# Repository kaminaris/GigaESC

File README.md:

# GigaESC - 40s 400A

GigaESC - Based upon the VESC®*-Project VESC is a registered TM, owned by Benjamin Vedder

* Modular design
* Logic board
* Separate Power Stage (Mosfet) board
* 40s capable
* Up to 188V (Mosfets and caps up to 200V)
* Up to 300A (depending on choice of mosfets)
* Hall sensor current measurement or low side shunts
* Built in IMU - LSM6DS3TR-C
* Optional Hardware current protection
* Designed for easy manufacturing at JLCPcb (KiCad Fabrication Toolkit)

Licensed under [Creative Commons Attribution-NonCommercial-ShareAlike 4.0 International License](https://creativecommons.org/licenses/by-nc-sa/4.0/legalcode.en)

# ⚠️Please do not order before contacting me on discord️⚠️

https://discord.gg/embedded

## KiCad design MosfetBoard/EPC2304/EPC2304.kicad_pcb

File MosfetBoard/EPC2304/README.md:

# GigaESC - EPC2304

---

# ⚠️Please do not order before contacting me on discord️⚠️

this is a very hard board to solder requires:

- Good knowledge of microsoldering
- **A microscope**
- Hot air capable of reaching 450°C
- A very thin soldering iron tip
- An oscilloscope

## GaN Soldering procedure

Use 60/40 solder from a reputable source. Trying to use lead-free solder by hand will be extremely difficult. Using poor-quality products will also result in failure, and this applies to flux as well.

This board has 4 layers, so it can absorb a lot of heat. Using high-quality solder is essential because the board is very sensitive to cold joints.

Having a good soldering iron is crucial and can make the difference between success and failure.

To solder GaN mosfets i strongly recommend using soldering paste instead, everything else can be done with wire tin.

1. Apply solder paste with flux on the footprint.
2. Position the GaN mosfet in place.
3. Use hot air until the solder melts and the GaN device is securely in place, applying gentle pressure to ensure proper contact.
4. Remove any excess solder with a soldering iron.
5. Allow the solder to cool down.

**[Repeat]**

1. Heat the solder joint again with hot air.
2. Apply flux.
3. Use tweezers to gently swirl the MOSFET, ensuring each pad has an equal amount of solder.
4. Reposition the MOSFET properly.
5. Allow the solder to cool down.

**[Repeat until the GaN mosfet self-aligns perfectly.]**

**⚠️While doing soldering procedure, make sure there are no microblobs of solder underneath mosfets.**
This may take a couple of tries to get it right.

## Testing procedure

1. Check with a multimeter the following parameters:
    - Resistance between + and - terminals: Should be very high, nearly open loop.
    - Resistance between each phase to ground: Should be greater than 40 kOhms.
    - Resistance between each phase to VBat+: Should be in the megaohms range.
    - Phase comparison: Each phase should have similar resistance readings to the others.
    - Gate connection check: Ensure each gate connects to the main PL and PH lines (this can be verified from the top of the PCB).
2. If electrically everything seems fine, connect to the main board and turn on the VESC:
    - Error code check: If any error code appears, there may be an issue, most commonly cold joints.
    - Current offset measurement:
        - Measure current offsets before doing anything with the VESC. 
        - They should all be within +/-10 LSB and around 2070
         
3. Connect the motor and measure its RL properties:
    - If you observe any abnormal values, such as very high inductance:
       - Check and fix any cold joints.
       - Use a multimeter to ensure each current sensor at idle is outputting about 1.65V.
       - Ensure each current sensor is receiving 5V.
4. Once any initial problems are resolved:
    - Set the current to the lowest possible value in FOC -> General and perform a full detection until all parameters are green and appear reasonable:
    
    - If you have another VESC, compare results with it. It will depend on motor itself so do not compare them to mine.
    - Perform a short double pulse test, for example: double_pulse 100 10 5 10. Confirm both edges look okay and are not overshooting.
    - Perform the motor detection.

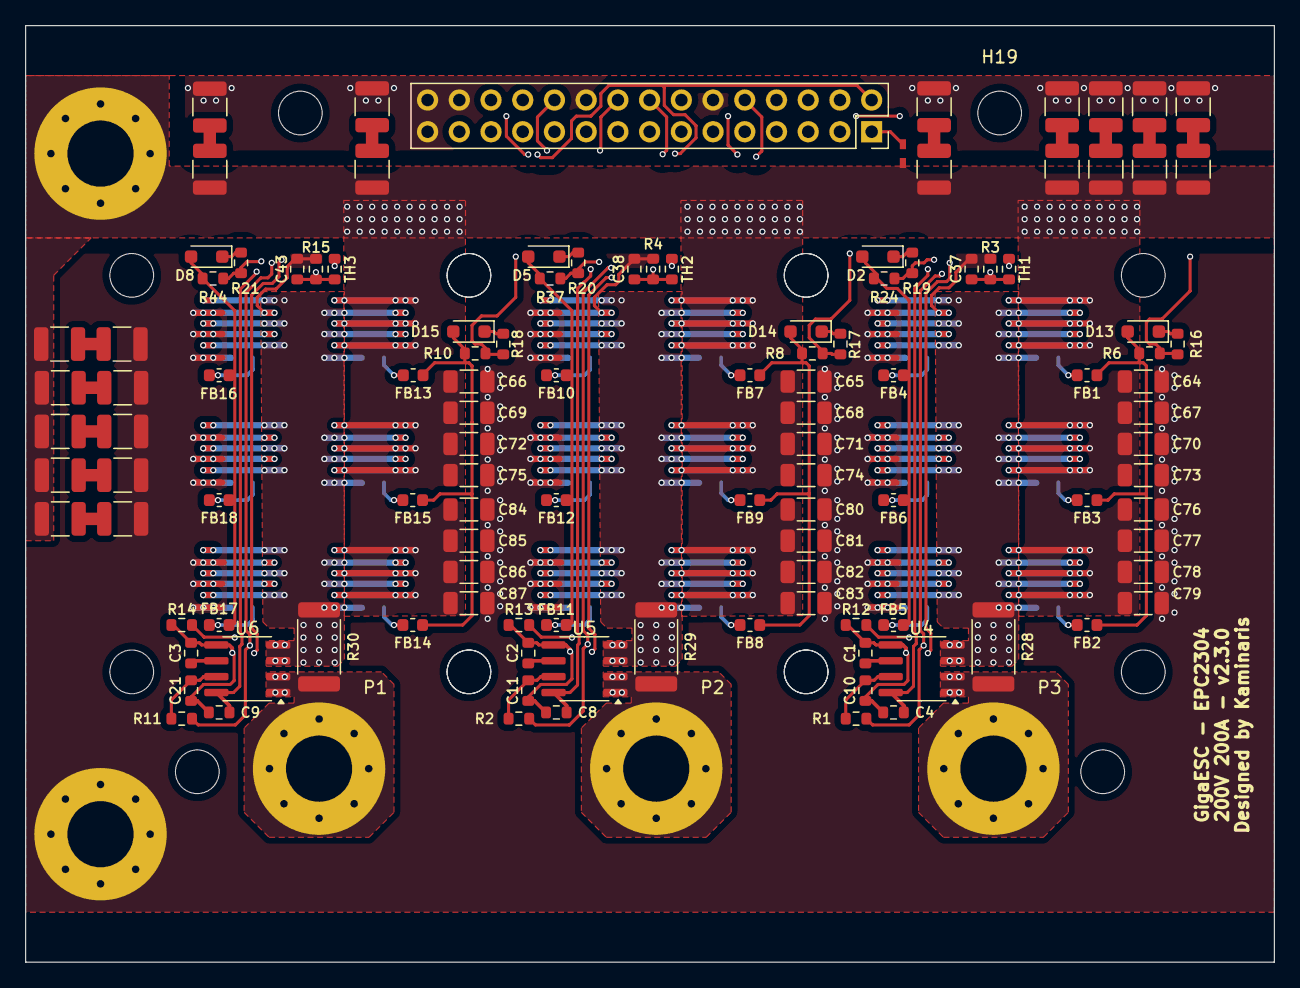
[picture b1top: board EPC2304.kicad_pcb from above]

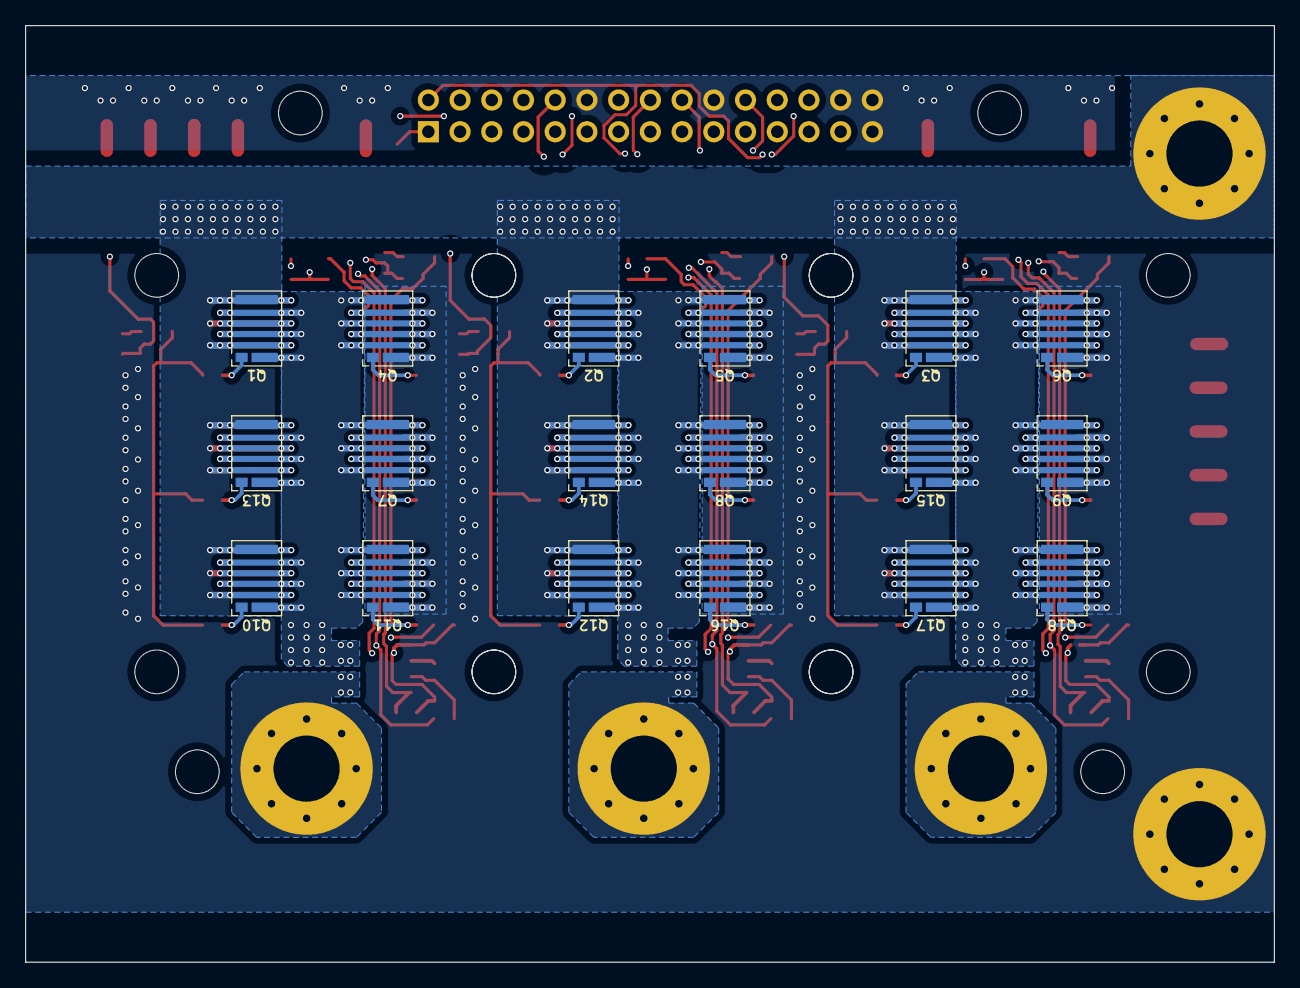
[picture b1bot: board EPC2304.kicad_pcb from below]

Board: 4 copper layers, 100.0 x 75.0 mm, 155 parts (18 on the bottom side), 74 nets.

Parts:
C1, C2, C3: 10n; C_0603_1608Metric_L
C4, C8, C9: 100n; C_0603_1608Metric_L
C10, C11, C21: 1n; C_0603_1608Metric_L
C37, C38, C43: 1u; C_0603_1608Metric_L
C64, C65, C66, C67, C68, C69, C70, C71, C72, C73, C74, C75, C76, C77, C78, C79, C80, C81, C82, C83, C84, C85, C86, C87: 200V 220n; C_1206_3216Metric
C88, C89, C90, C91, C92, C93, C94, C95, C96, C97, C98, C99, C100, C101, C102, C103, C104, C105, C106, C107, C108, C109, C110, C111: 10u 100V; C_1210_3225Metric
D2, D5, D8, D13, D14, D15: 1N5819WS; D_SOD-323_HandSoldering
FB1, FB2, FB3, FB4, FB5, FB6, FB7, FB8, FB9, FB10, FB11, FB12, FB13, FB14, FB15, FB16, FB17, FB18: BLM18AG331SN1D; L_0603_1608Metric
H1, H2, H3: PhaseConnector; MountingHole_5.3mm_M5_Pad_Via
H4, H6: MountingHole_Pad; MountingHole_5.3mm_M5_Pad_Via
H5, H7, H8, H9, H10, H11, H12, H13, H14, H15, H16, H17, H18, H19, H20, H21: MountingHole; CapHead_3.5mm
J2: LogicConnector; PinSocket_2x15_P2.54mm_Vertical
JP1: Jumper_2_Open; SolderJumper0.5mm_Open
Q1, Q2, Q3, Q4, Q5, Q6, Q7, Q8, Q9, Q10, Q11, Q12, Q13, Q14, Q15, Q16, Q17, Q18: EPC2304
R1, R2, R11: 4.7k; R_0603_1608Metric
R3, R4, R15: 10k; R_0603_1608Metric
R6, R8, R10, R24, R37, R44: 6.8; R_0603_1608Metric
R12, R13, R14: 9.1k; R_0603_1608Metric
R16, R17, R18, R19, R20, R21: 10; R_0603_1608Metric
R28, R29, R30: 0.3m; R_2512_6332Metric
TH1, TH2, TH3: NCP18XH103F03RB; R_0603_1608Metric
U4, U5, U6: MT9223CT-50BR5; SOIC-8_3.9x4.9mm_P1.27mm

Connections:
+BATT: C64.1, C65.1, C66.1, C67.1, C68.1, C69.1, C70.1, C71.1, C72.1, C73.1, C74.1, C75.1, C76.1, C77.1, C78.1, C79.1, C80.1, C81.1, C82.1, C83.1, C84.1, C85.1, C86.1, C87.1, C88.1, C90.1, C92.1, C94.1, C96.1, C98.1, C100.1, C102.1, C104.1, C106.1, C108.1, C110.1, H6.1, JP1.1 (A), Q1.3 (D), Q1.5 (D), Q1.7 (D), Q2.3 (D), Q2.5 (D), Q2.7 (D), Q3.3 (D), Q3.5 (D), Q3.7 (D), Q10.3 (D), Q10.5 (D), Q10.7 (D), Q12.3 (D), Q12.5 (D), Q12.7 (D), Q13.3 (D), Q13.5 (D), Q13.7 (D), Q14.3 (D), Q14.5 (D), Q14.7 (D), Q15.3 (D), Q15.5 (D), Q15.7 (D), Q17.3 (D), Q17.5 (D), Q17.7 (D)
-BATT: C37.2, C38.2, C43.2, C64.2, C65.2, C66.2, C67.2, C68.2, C69.2, C70.2, C71.2, C72.2, C73.2, C74.2, C75.2, C76.2, C77.2, C78.2, C79.2, C80.2, C81.2, C82.2, C83.2, C84.2, C85.2, C86.2, C87.2, C89.2, C91.2, C93.2, C95.2, C97.2, C99.2, C101.2, C103.2, C105.2, C107.2, C109.2, C111.2, H4.1, J2.12, J2.20, J2.28, J2.29, J2.30, Q4.2 (S), Q4.4 (S), Q4.6 (S), Q5.2 (S), Q5.4 (S), Q5.6 (S), Q6.2 (S), Q6.4 (S), Q6.6 (S), Q7.2 (S), Q7.4 (S), Q7.6 (S), Q8.2 (S), Q8.4 (S), Q8.6 (S), Q9.2 (S), Q9.4 (S), Q9.6 (S), Q11.2 (S), Q11.4 (S), Q11.6 (S), Q16.2 (S), Q16.4 (S), Q16.6 (S), Q18.2 (S), Q18.4 (S), Q18.6 (S), R3.2, R4.2, R15.2
/3.3V: J2.2, TH1.1, TH2.1, TH3.1
/5V: C4.2, C8.2, C9.2, J2.4, U4.8 (VCC), U5.8 (VCC), U6.8 (VCC)
/PH1: J2.6, R6.1, R16.1
/PH2: J2.14, R8.1, R17.1
/PH3: J2.22, R10.1, R18.1
/PHASE1: J2.8, Q1.2 (S), Q1.4 (S), Q1.6 (S), Q4.3 (D), Q4.5 (D), Q4.7 (D), Q7.3 (D), Q7.5 (D), Q7.7 (D), Q10.2 (S), Q10.4 (S), Q10.6 (S), Q11.3 (D), Q11.5 (D), Q11.7 (D), Q13.2 (S), Q13.4 (S), Q13.6 (S), R28.1, U4.3 (IP-), U4.4 (IP-)
/PHASE2: J2.16, Q2.2 (S), Q2.4 (S), Q2.6 (S), Q5.3 (D), Q5.5 (D), Q5.7 (D), Q8.3 (D), Q8.5 (D), Q8.7 (D), Q12.2 (S), Q12.4 (S), Q12.6 (S), Q14.2 (S), Q14.4 (S), Q14.6 (S), Q16.3 (D), Q16.5 (D), Q16.7 (D), R29.1, U5.3 (IP-), U5.4 (IP-)
/PHASE3: J2.24, Q3.2 (S), Q3.4 (S), Q3.6 (S), Q6.3 (D), Q6.5 (D), Q6.7 (D), Q9.3 (D), Q9.5 (D), Q9.7 (D), Q15.2 (S), Q15.4 (S), Q15.6 (S), Q17.2 (S), Q17.4 (S), Q17.6 (S), Q18.3 (D), Q18.5 (D), Q18.7 (D), R30.1, U6.3 (IP-), U6.4 (IP-)
/PL1: J2.10, R19.1, R24.1
/PL2: J2.18, R20.1, R37.1
/PL3: J2.26, R21.1, R44.1
/PhaseMosfets1/HIGH: D13.2 (A), FB1.1, FB2.1, FB3.1, R6.2
/PhaseMosfets1/LOW: D2.2 (A), FB4.1, FB5.1, FB6.1, R24.2
/PhaseMosfets1/MOS_TEMP: C37.1, J2.5, R3.1, TH1.2
/PhaseMosfets1/PHASE_OUT: H1.1, R28.2, U4.1 (IP+), U4.2 (IP+)
/PhaseMosfets1/SH+: J2.11, R1.1, R12.2
/PhaseMosfets1/SH-: C1.2, C4.1, C10.2, J2.9, R12.1, U4.5 (GND)
/PhaseMosfets2/HIGH: D14.2 (A), FB7.1, FB8.1, FB9.1, R8.2
/PhaseMosfets2/LOW: D5.2 (A), FB10.1, FB11.1, FB12.1, R37.2
/PhaseMosfets2/MOS_TEMP: C38.1, J2.13, R4.1, TH2.2
/PhaseMosfets2/PHASE_OUT: H2.1, R29.2, U5.1 (IP+), U5.2 (IP+)
/PhaseMosfets2/SH+: J2.19, R2.1, R13.2
/PhaseMosfets2/SH-: C2.2, C8.1, C11.2, J2.17, R13.1, U5.5 (GND)
/PhaseMosfets3/HIGH: D15.2 (A), FB13.1, FB14.1, FB15.1, R10.2
/PhaseMosfets3/LOW: D8.2 (A), FB16.1, FB17.1, FB18.1, R44.2
/PhaseMosfets3/MOS_TEMP: C43.1, J2.21, R15.1, TH3.2
/PhaseMosfets3/PHASE_OUT: H3.1, R30.2, U6.1 (IP+), U6.2 (IP+)
/PhaseMosfets3/SH+: J2.27, R11.1, R14.2
/PhaseMosfets3/SH-: C3.2, C9.1, C21.2, J2.25, R14.1, U6.5 (GND)
unnamed: C88.2, C89.1
unnamed: C90.2, C91.1
unnamed: C92.2, C93.1
unnamed: C94.2, C95.1
unnamed: C96.2, C97.1
unnamed: C98.2, C99.1
unnamed: C100.2, C101.1
unnamed: C102.2, C103.1
unnamed: C104.2, C105.1
unnamed: C106.2, C107.1
unnamed: C108.2, C109.1
unnamed: C110.2, C111.1
unnamed: D2.1 (K), R19.2
unnamed: D5.1 (K), R20.2
unnamed: D8.1 (K), R21.2
unnamed: D13.1 (K), R16.2
unnamed: D14.1 (K), R17.2
unnamed: D15.1 (K), R18.2
unnamed: J2.1, JP1.2 (B)
unnamed: FB1.2, Q1.1 (G)
unnamed: FB7.2, Q2.1 (G)
unnamed: FB13.2, Q3.1 (G)
unnamed: FB4.2, Q4.1 (G)
unnamed: FB10.2, Q5.1 (G)
unnamed: FB16.2, Q6.1 (G)
unnamed: FB6.2, Q7.1 (G)
unnamed: FB12.2, Q8.1 (G)
unnamed: FB18.2, Q9.1 (G)
unnamed: FB2.2, Q10.1 (G)
unnamed: FB5.2, Q11.1 (G)
unnamed: FB8.2, Q12.1 (G)
unnamed: FB3.2, Q13.1 (G)
unnamed: FB9.2, Q14.1 (G)
unnamed: FB15.2, Q15.1 (G)
unnamed: FB11.2, Q16.1 (G)
unnamed: FB14.2, Q17.1 (G)
unnamed: FB17.2, Q18.1 (G)
unnamed: C1.1, U4.6 (FILTER)
unnamed: C10.1, R1.2, U4.7 (VIOUT)
unnamed: C2.1, U5.6 (FILTER)
unnamed: C11.1, R2.2, U5.7 (VIOUT)
unnamed: C3.1, U6.6 (FILTER)
unnamed: C21.1, R11.2, U6.7 (VIOUT)

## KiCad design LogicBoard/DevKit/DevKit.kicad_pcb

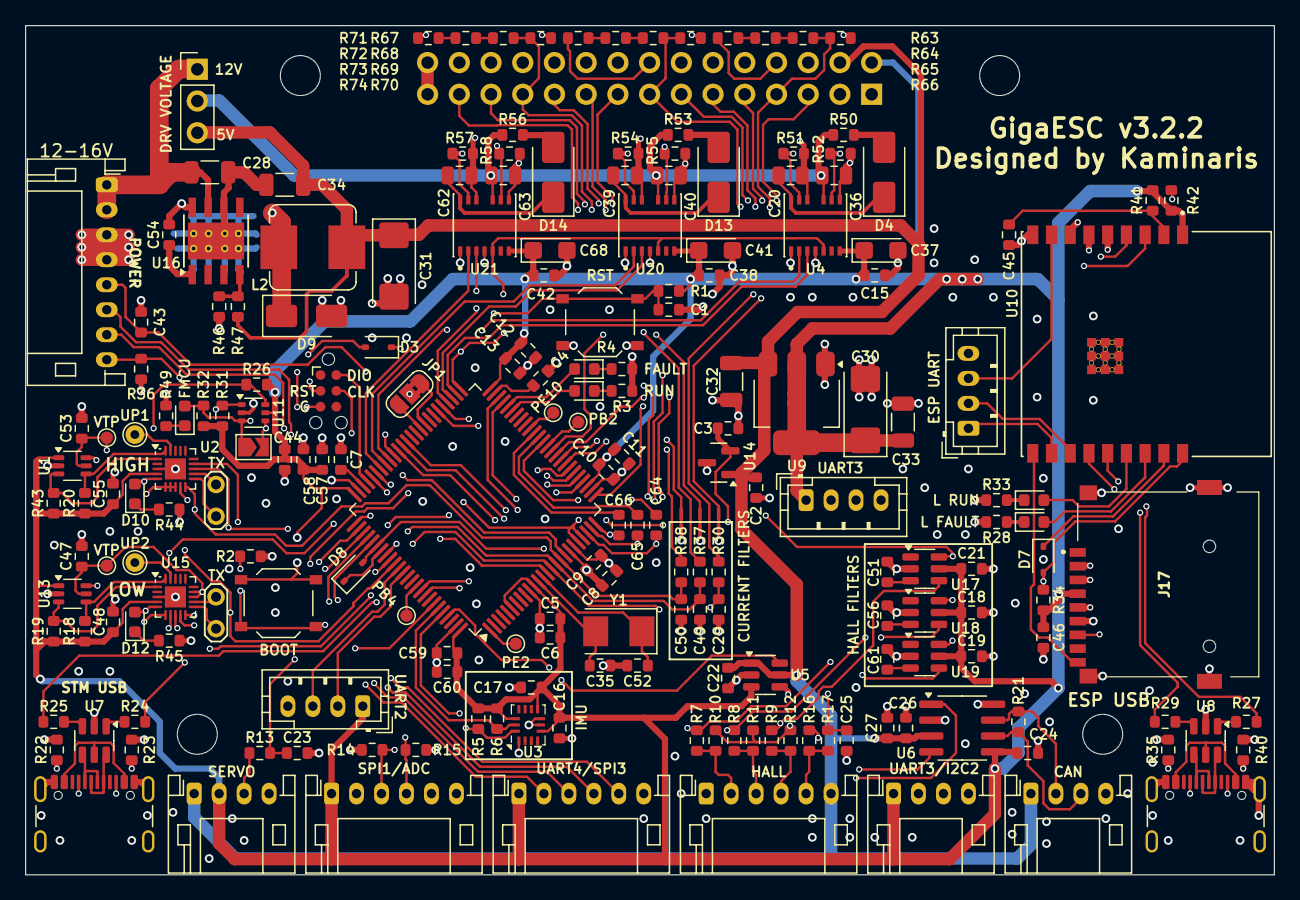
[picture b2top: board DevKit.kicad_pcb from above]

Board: 4 copper layers, 100.0 x 68.0 mm, 208 parts (1 on the bottom side), 170 nets.

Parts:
C1, C6, C9, C11, C13, C15, C16, C17, C18, C19, C21, C22, C23, C24, C26, C38, C42, C44, C45, C46, C58, C60, C64, C65, C66: 100n; C_0603_1608Metric_L
C2, C3, C4, C7, C47, C48, C53, C55: 1u; C_0603_1608Metric_L
C5, C8, C10, C12, C54, C57, C59: 10n; C_0603_1608Metric_L
C20, C36, C39, C40, C62, C63: 4.7u 25v; C_0805_2012Metric
C25, C43, C51, C56, C61: 1n; C_0603_1608Metric_L
C27: 2.2u; C_0603_1608Metric_L
C28, C32, C33, C34: 22u 25V; C_1206_3216Metric
C29, C49, C50: 2.2n; C_0603_1608Metric_L
C30, C31: 100uF 10V Tant; CP_EIA-6032-28_Kemet-C
C35, C52: 20p; R_0603_1608Metric
C37, C41, C68: 47u 6.3v Tant; CP_EIA-3216-18_Kemet-A
D1, D5: L RUN; LED_0603_1608Metric
D2, D6, D10, D12: L FAULT; LED_0603_1608Metric
D3, D7, D8: 1N5819WS; D_SOD-323
D4, D13, D14: SS520F; D_SMA
D9: SS34; D_SMA
D11: DRV-FAULT; LED_0603_1608Metric
H1, H2, H3, H4: MountingHole; MountingHole_3.2mm_M3_ISO14580
J1: ServoConn; JST_PH_S4B-PH-K_1x04_P2.00mm_Horizontal
J2: AuxConn; JST_PH_S8B-PH-K_1x08_P2.00mm_Horizontal
J4, J21: UARTDBG; TestPoint_2Pads_Pitch2.54mm_Drill0.8mm
J5: HallConn; JST_PH_S6B-PH-K_1x06_P2.00mm_Horizontal
J6: UARTConn; JST_PH_S4B-PH-K_1x04_P2.00mm_Horizontal
J7: JTAG; Tag-Connect_TC2030-IDC-NL_2x03_P1.27mm_Vertical
J8: CANConn; JST_PH_S4B-PH-K_1x04_P2.00mm_Horizontal
J9, J13: USBC Socket; USB_C_Receptacle_GCT_USB4105-xx-A_16P_TopMnt_Horizontal
J10: LogicConnector; PinHeader_2x15_P2.54mm_Vertical
J11: SPI1Conn; JST_PH_S6B-PH-K_1x06_P2.00mm_Horizontal
J12: UART2Conn; JST_PH_B4B-PH-K_1x04_P2.00mm_Vertical
J15: ESPUartConn; JST_PH_B4B-PH-K_1x04_P2.00mm_Vertical
J17: MicroSD; TF01A
J20: SPI3Conn; JST_PH_S6B-PH-K_1x06_P2.00mm_Horizontal
J22: UART3Conn; JST_PH_B4B-PH-K_1x04_P2.00mm_Vertical
J23: DriverVoltageSelect; PinHeader_1x03_P2.54mm_Vertical
JP1: ServoSelector; SolderJumper-3_P1.3mm_Bridged2Bar12_RoundedPad1.0x1.5mm_Num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
JP2, JP3, JP4: GND Jumper; SolderJumper0.3mm
JP5: OV BYPASS; SolderJumper-2_P1.3mm_Open_TrianglePad1.0x1.5mm
L2: 15uH; L_Bourns_SRP7028A_7.3x6.6mm
R1, R3, R4, R7, R8, R9, R10, R11, R12, R14, R15, R16, R17, R26, R28, R31, R32, R33, R34, R36, R41, R42, R44, R45, R47, R49: 10k; R_0603_1608Metric
R2, R46: 3.3k; R_0603_1608Metric
R5, R6, R18, R19, R20, R43, R51, R52, R54, R55, R57, R58: 4.7k; R_0603_1608Metric
R13: 220; R_0603_1608Metric
R21: 120; R_0603_1608Metric
R22, R23, R35, R40: 5.1k; R_0603_1608Metric
R24, R25, R27, R29: 22; R_0603_1608Metric
R30, R37, R38: 150; R_0603_1608Metric
R50, R53, R56: 2.2; R_0603_1608Metric
R63, R64, R65, R67, R68, R69, R71, R72, R73: 348k; R_0603_1608Metric
R66, R70, R74: 18.7k; R_0603_1608Metric
SW1: BOOT; SW_Push_1P1T_XKB_TS-1187A
SW3: RST; SW_Push_1P1T_XKB_TS-1187A
TP2: TestPoint; TestPoint_Pad_D1.0mm
TP3, TP4: VTP; TestPoint_Pad_D1.0mm
TP5, TP6: UPDI; TestPoint_THTPad_D1.5mm_Drill0.7mm
TP7: PE2; TestPoint_Pad_D1.0mm
TP8: PB2; TestPoint_Pad_D1.0mm
TP9: PE10; TestPoint_Pad_D1.0mm
U1, U13: TPL0401B-10DCKR; Texas_R-PDSO-G6
U2, U15: ATTINY1616-MNR; VQFN-20-1EP_3x3mm_P0.4mm_EP1.7x1.7mm
U3: LSM6DS3TR-C; Bosch_LGA-14_3x2.5mm_P0.5mm
U4, U20, U21: 2EDF7275KXUMA1; IC_2EDF7275KXUMA2
U5, U17, U18, U19: RS2057XH; SOT-23-6
U6: TJA1050T/CM,118; SOIC-8_3.9x4.9mm_P1.27mm
U7, U8: USBLC6-2SC6; SOT-23-6
U9: AMS1117-3.3; SOT-223-3_TabPin2
U10: ESP32-C3-WROOM-02-N4; MODULE_ESP32-C3-WROOM-02-H4
U11: SN74LVC1G332DCKR; SOT-363_SC-70-6
U12: STM32F407VGT6; LQFP-100_14x14mm_P0.5mm
U14: REF3033AIDBZR; SOT-23
U16: TPS5430DDAR; TI_SO-PowerPAD-8_ThermalVias
Y1: X50328MSB2GI; Crystal_SMD_5032-2Pin_5.0x3.2mm

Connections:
+3.3REF: C3.1, U1.6 (H), U12.21 (VREF+), U12.22 (VDDA), U13.6 (H), U14.2 (Vout)
+3.3V: C5.1, C6.1, C8.1, C9.1, C10.1, C11.1, C12.1, C13.1, C15.2, C16.1, C17.1, C18.1, C19.1, C21.1, C24.1, C30.1, C33.1, C37.1, C38.2, C41.1, C42.2, C44.1, C46.1, C48.1, C55.1, C57.1, C58.1, C59.1, C60.1, C68.1, J1.2, J6.1, J10.2, J11.1, J12.1, J17.4 (VDD), J20.1, J22.1, R1.1, R5.1, R6.1, R16.2, R18.1, R19.1, R20.1, R26.1, R31.1, R32.1, R34.1, R41.2, R42.1, R43.1, SW1.1, U1.1 (VDD), U2.4 (VCC), U3.5 (VDDIO), U3.8 (VDD), U3.12 (CSB), U4.7 (VDDI), U5.3 (NC), U6.5 (VIO), U9.2 (VO), U10.1 (3V3), U11.5 (VCC), U12.6 (VBAT), U12.11 (VDD), U12.19 (VDD), U12.28 (VDD), U12.50 (VDD), U12.75 (VDD), U12.100 (VDD), U13.1 (VDD), U15.4 (VCC), U17.5 (V+), U18.5 (V+), U19.5 (V+), U20.7 (VDDI), U21.7 (VDDI)
+5V: C2.1, C22.1, C26.1, C27.1, C31.1, C32.1, C34.1, J1.1, J5.6, J8.1, J10.4, J23.3, L2.2, R47.2, U5.1 (NO), U5.5 (V+), U6.3 (VCC), U9.3 (VI), U14.1 (Vin)
+15V: C28.1, J2.1, J2.2, J23.1, U16.7 (VIN)
/CURR1-: J10.9, JP4.2 (B)
/CURR2-: J10.17, JP3.2 (B)
/CURR3-: J10.25, JP2.2 (B)
/DriverSocketPhase1/PH: J10.6, R51.2, U4.12 (OUTA)
/DriverSocketPhase1/PHASE: C20.2, J10.8, R51.1, R63.1, U4.11 (GNDA)
/DriverSocketPhase1/PHASE GROUND: C36.2, J10.12, R52.1, U4.8 (GNDB)
/DriverSocketPhase1/PL: J10.10, R52.2, U4.9 (OUTB)
/DriverSocketPhase2/PH: J10.14, R54.2, U20.12 (OUTA)
/DriverSocketPhase2/PHASE: C39.2, J10.16, R54.1, R67.1, U20.11 (GNDA)
/DriverSocketPhase2/PHASE GROUND: C40.2, J10.20, R55.1, U20.8 (GNDB)
/DriverSocketPhase2/PL: J10.18, R55.2, U20.9 (OUTB)
/DriverSocketPhase3/PH: J10.22, R57.2, U21.12 (OUTA)
/DriverSocketPhase3/PHASE: C62.2, J10.24, R57.1, R71.1, U21.11 (GNDA)
/DriverSocketPhase3/PHASE GROUND: C63.2, J10.28, R58.1, U21.8 (GNDB)
/DriverSocketPhase3/PL: J10.26, R58.2, U21.9 (OUTB)
/HardwareProtection/ComparatorHigh/AT RX: J21.2, U2.11 (PB3)
/HardwareProtection/ComparatorHigh/AT TX: J21.1, U2.12 (PB2)
/HardwareProtection/ComparatorHigh/ATTINY SCL: R43.2, U1.3 (SCL), U2.1 (PA2)
/HardwareProtection/ComparatorHigh/ATTINY SDA: R20.2, U1.4 (SDA), U2.20 (PA1)
/HardwareProtection/ComparatorHigh/CMP1-: C53.1, TP3.1, U1.5 (W), U2.6 (PA5), U2.7 (PA6), U2.8 (PA7)
/HardwareProtection/ComparatorHigh/LATCH OUT: D10.2 (A), R26.2, U2.5 (PA4), U11.6
/HardwareProtection/ComparatorLow/AT RX: J4.2, U15.11 (PB3)
/HardwareProtection/ComparatorLow/AT TX: J4.1, U15.12 (PB2)
/HardwareProtection/ComparatorLow/ATTINY SCL: R19.2, U13.3 (SCL), U15.1 (PA2)
/HardwareProtection/ComparatorLow/ATTINY SDA: R18.2, U13.4 (SDA), U15.20 (PA1)
/HardwareProtection/ComparatorLow/CMP1+: C47.1, TP4.1, U13.5 (W), U15.10 (PB4), U15.13 (PB1), U15.14 (PB0)
/HardwareProtection/ComparatorLow/LATCH OUT: D12.2 (A), R31.2, U11.1, U15.5 (PA4)
ADC EXT: J11.3, R14.2, U12.30 (PA5)
ADC EXT2: J11.4, R15.1, U12.31 (PA6)
AUX ENABLE: J2.6, U12.83 (PD2)
AUX FAULT: J2.7, U12.84 (PD3)
BOOT: R2.1, SW1.2, U12.94 (BOOT0)
CAN2 RX: D7.2 (A), D8.2 (A), R34.2, U10.18 (IO0), U12.81 (PD0)
CAN2 TX: D8.1 (K), U12.82 (PD1)
CAN RX: U6.4 (RXD), U12.91 (PB5)
CAN TX: U6.1 (TXD), U12.92 (PB6)
CLEAR HW FAULT: J2.8, R36.1, U2.9 (PB5), U12.85 (PD4), U15.9 (PB5)
CURR1: J10.11, R30.2
CURR1 FILTERED: C29.1, R30.1, U2.13 (PB1), U12.15 (PC0), U15.7 (PA6)
CURR2: J10.19, R37.2
CURR2 FILTERED: C49.1, R37.1, U2.14 (PB0), U12.16 (PC1), U15.8 (PA7)
CURR3: J10.27, R38.2
CURR3 FILTERED: C50.2, R38.1, U2.10 (PB4), U12.17 (PC2), U15.6 (PA5)
DRIVER POWER: C36.1, C40.1, C63.1, J23.2, R50.1, R53.1, R56.1, U4.10 (VDDB), U20.10 (VDDB), U21.10 (VDDB)
ESP FAULT LED: D6.2 (A), U10.16 (IO2)
ESP IO9: J15.3, U10.8 (IO9)
ESP MISO: J17.7 (DAT0), U10.5 (IO6)
ESP MOSI: J17.3 (CMD), U10.3 (IO4)
ESP RUN LED: D5.2 (A), U10.15 (IO3)
ESP RX: J15.1, U10.11 (RXD)
ESP SCK: J17.5 (CLK), U10.4 (IO5)
ESP SD CS: J17.2 (DAT3/CD), U10.6 (IO7)
ESP SD DETECT: J17.9 (DET), U10.10 (IO10)
ESP TX: J15.2, U10.12 (TXD)
ESP USB D+: R27.2, U10.14 (IO19)
ESP USB D-: R29.2, U10.13 (IO18)
GND: C1.2, C2.2, C3.2, C4.2, C5.2, C6.2, C7.2, C8.2, C9.2, C10.2, C11.2, C12.2, C13.2, C15.1, C16.2, C17.2, C18.2, C19.2, C21.2, C22.2, C23.2, C24.2, C25.2, C26.2, C27.2, C28.2, C29.2, C30.2, C31.2, C32.2, C33.2, C34.2, C35.1, C37.2, C38.1, C41.2, C42.1, C43.2, C44.2, C45.2, C46.2, C47.2, C48.2, C49.2, C50.1, C51.1, C52.2, C53.2, C55.2, C56.1, C57.2, C58.2, C59.2, C60.2, C61.1, C68.2, D9.2 (A), J1.4, J2.3, J2.4, J5.1, J6.4, J7.5 (GND), J8.4, J9.A1 (GND), J9.A12 (GND), J9.B1 (GND), J9.B12 (GND), J9.S1 (SHIELD), J10.29, J10.30, J11.6, J12.4, J13.A1 (GND), J13.A12 (GND), J13.B1 (GND), J13.B12 (GND), J13.S1 (SHIELD), J15.4, J17.6 (VSS), J17.10 (SHIELD), J20.6, J22.4, JP2.1 (A), JP3.1 (A), JP4.1 (A), R2.2, R3.2, R4.2, R14.1, R15.2, R22.1, R23.1, R28.2, R33.2, R35.1, R36.2, R40.1, R44.2, R45.2, R46.2, R49.2, R66.2, R70.2, R74.2, SW3.2, U1.2 (GND), U2.3 (GND), U2.21 (GND), U3.1 (SDO), U3.6 (GNDIO), U3.7 (GND), U4.1 (GNDI), U4.4 (SLDON), U5.2 (GND), U6.2 (GND), U6.8 (S), U7.2 (GND), U8.2 (GND), U9.1 (GND), U10.9 (GND), U10.19 (GND), U10.20 (GND), U10.21 (GND), U10.22 (GND), U10.23 (GND), U10.24 (GND), U10.25 (GND), U10.26 (GND), U10.27 (GND), U10.28 (GND), U10.29 (GND), U10.30 (GND), U10.31 (GND), U10.32 (GND), U10.33 (GND), U10.34 (GND), U10.35 (GND), U10.36 (GND), U10.37 (GND), U10.38 (GND), U10.39 (GND), U11.2 (GND), U12.10 (VSS), U12.20 (VSSA), U12.27 (VSS), U12.74 (VSS), U12.99 (VSS), U13.2 (GND), U14.3 (GND), U15.3 (GND), U15.21 (GND), U16.6 (GND), U16.9 (GNDPAD), U17.2 (GND), U18.2 (GND), U19.2 (GND), U20.1 (GNDI), U20.4 (SLDON), U21.1 (GNDI), U21.4 (SLDON)
H1: U4.2 (INA), U12.67 (PA8)
H2: U12.68 (PA9), U20.2 (INA)
H3: U12.69 (PA10), U21.2 (INA)
HALL1: R9.1, U12.63 (PC6), U17.4 (COM)
HALL1 IN: J5.4, R9.2, R12.1
HALL2: R8.1, U12.64 (PC7), U18.4 (COM)
HALL2 IN: J5.3, R8.2, R11.1
HALL3: R7.1, U12.65 (PC8), U19.4 (COM)
HALL3 IN: J5.2, R7.2, R10.1
HALL FILTER ENABLE: U12.34 (PC5), U17.6 (IN), U18.6 (IN), U19.6 (IN)
I2C2 SCL/USART3 TX: J6.3, U12.47 (PB10)
I2C2 SDA/USART3 RX: J6.2, U12.48 (PB11)
IMU SCL: R6.2, U3.13 (SCx), U12.95 (PB8)
IMU SDA: R5.2, U3.14 (SDx), U12.96 (PB9)
IN V: C43.1, J2.5, U12.18 (PC3)
L1: U4.3 (INB), U12.52 (PB13)
L2: U12.53 (PB14), U20.3 (INB)
L3: U12.54 (PB15), U21.3 (INB)
LED FAULT: D2.2 (A), U12.46 (PE15)
LED RUN: D1.2 (A), U12.45 (PE14)
MOSTEMP1: J10.5, U12.26 (PA3)
MOSTEMP2: J10.13, U12.35 (PB0)
MOSTEMP3: J10.21, U12.36 (PB1)
NRST: C1.1, J7.3 (~RESET), R1.2, SW3.1, U12.14 (NRST)
unnamed: D1.1 (K), R3.1
unnamed: D2.1 (K), R4.1
unnamed: D3.2 (A), JP5.2 (B), U11.4
unnamed: D4.2 (A), R50.2
unnamed: C20.1, D4.1 (K), U4.13 (VDDA)
unnamed: D5.1 (K), R33.1
unnamed: D6.1 (K), R28.1
unnamed: D7.1 (K), U10.17 (IO1)
unnamed: C54.1, D9.1 (K), L2.1, U16.8 (PH)
unnamed: D10.1 (K), R44.1
unnamed: D11.1 (K), R49.1
unnamed: D12.1 (K), R45.1
unnamed: D13.2 (A), R53.2
unnamed: C39.1, D13.1 (K), U20.13 (VDDA)
unnamed: D14.2 (A), R56.2
unnamed: C62.1, D14.1 (K), U21.13 (VDDA)
unnamed: J1.3, R13.1
unnamed: J8.2, R21.2, U6.7 (CANH)
unnamed: J8.3, R21.1, U6.6 (CANL)
unnamed: J9.A5 (CC1), R22.2
unnamed: J9.B5 (CC2), R23.2
unnamed: J9.A6 (D+), J9.B6 (D+), U7.6 (I/O1)
unnamed: J9.A7 (D-), J9.B7 (D-), U7.4 (I/O2)
unnamed: J13.A5 (CC1), R35.2
unnamed: J13.B5 (CC2), R40.2
unnamed: J13.A6 (D+), J13.B6 (D+), U8.6 (I/O1)
unnamed: J13.A7 (D-), J13.B7 (D-), U8.4 (I/O2)
unnamed: JP1.1 (A), U12.59 (PD12)
unnamed: JP1.3 (B), U12.60 (PD13)
unnamed: R24.1, U7.1 (I/O1)
unnamed: R25.1, U7.3 (I/O2)
unnamed: R27.1, U8.1 (I/O1)
unnamed: R29.1, U8.3 (I/O2)
unnamed: R63.2, R64.1
unnamed: R64.2, R65.1
unnamed: R67.2, R68.1
unnamed: R68.2, R69.1
unnamed: R71.2, R72.1
unnamed: R72.2, R73.1
unnamed: TP5.1, U2.19 (~RESET/PA0)
unnamed: R10.2, R11.2, R12.2, U5.4 (COM)
unnamed: J9.A4 (VBUS), J9.A9 (VBUS), J9.B4 (VBUS), J9.B9 (VBUS), U7.5 (VBUS)
unnamed: J13.A4 (VBUS), J13.A9 (VBUS), J13.B4 (VBUS), J13.B9 (VBUS), U8.5 (VBUS)
unnamed: C45.1, R41.1, U10.2 (EN)
unnamed: R42.2, U10.7 (IO8)
unnamed: TP8.1, U12.37 (PB2)
unnamed: TP2.1, U12.90 (PB4)
unnamed: TP7.1, U12.1 (PE2)
unnamed: TP9.1, U12.41 (PE10)
unnamed: C35.2, U12.12 (PH0), Y1.2
unnamed: C52.1, U12.13 (PH1), Y1.1
unnamed: C4.1, U12.49 (VCAP_1)
unnamed: C7.1, U12.73 (VCAP_2)
unnamed: TP6.1, U15.19 (~RESET/PA0)
unnamed: C54.2, U16.1 (BOOT)
unnamed: R46.1, R47.1, U16.4 (VSENSE)
unnamed: C51.2, U17.3 (NC)
unnamed: C56.2, U18.3 (NC)
unnamed: C61.2, U19.3 (NC)
PHASE FILTER ENABLE1: C64.2, U12.38 (PE7)
PHASE FILTER ENABLE2: C65.2, U12.39 (PE8)
PHASE FILTER ENABLE3: C66.2, U12.40 (PE9)
POWER STAGE DISABLE: D11.2 (A), JP5.1 (A), R32.2, U11.3, U12.66 (PC9)
POWER STAGE LOCKOUT: D3.1 (K), U4.5 (DISABLE), U12.51 (PB12), U20.5 (DISABLE), U21.5 (DISABLE)
SENSOR VOLTAGE SELECT: U5.6 (IN), U12.97 (PE0)
SERVO: C23.1, JP1.2 (C), R13.2
SPI1 MOSI: J11.5, U12.32 (PA7)
SPI1 NSS: J11.2, U12.29 (PA4)
SPI3 MISO: J20.4, U12.79 (PC11)
SPI3 MOSI: J20.5, U12.80 (PC12)
SPI3 NSS: J20.2, U12.77 (PA15)
SPI3 SCK: J20.3, U12.78 (PC10)
SWCLK: J7.4 (SWCLK), U12.76 (PA14)
SWDIO: J7.2 (SWDIO), U12.72 (PA13)
TEMPMOTOR: C25.1, R17.2, U12.33 (PC4)
TEMPMOTOR IN: J5.5, R16.1, R17.1
UART3 RX: J22.2, U12.56 (PD9)
UART3 TX: J22.3, U12.55 (PD8)
USART2 RX: J12.2, U12.87 (PD6)
USART2 TX: J12.3, U12.86 (PD5)
USBD+: R24.2, U12.71 (PA12)
USBD-: R25.2, U12.70 (PA11)
VSENSE1: C64.1, J10.7, R65.2, R66.1, U12.23 (PA0)
VSENSE2: C65.1, J10.15, R69.2, R70.1, U12.24 (PA1)
VSENSE3: C66.1, J10.23, R73.2, R74.1, U12.25 (PA2)

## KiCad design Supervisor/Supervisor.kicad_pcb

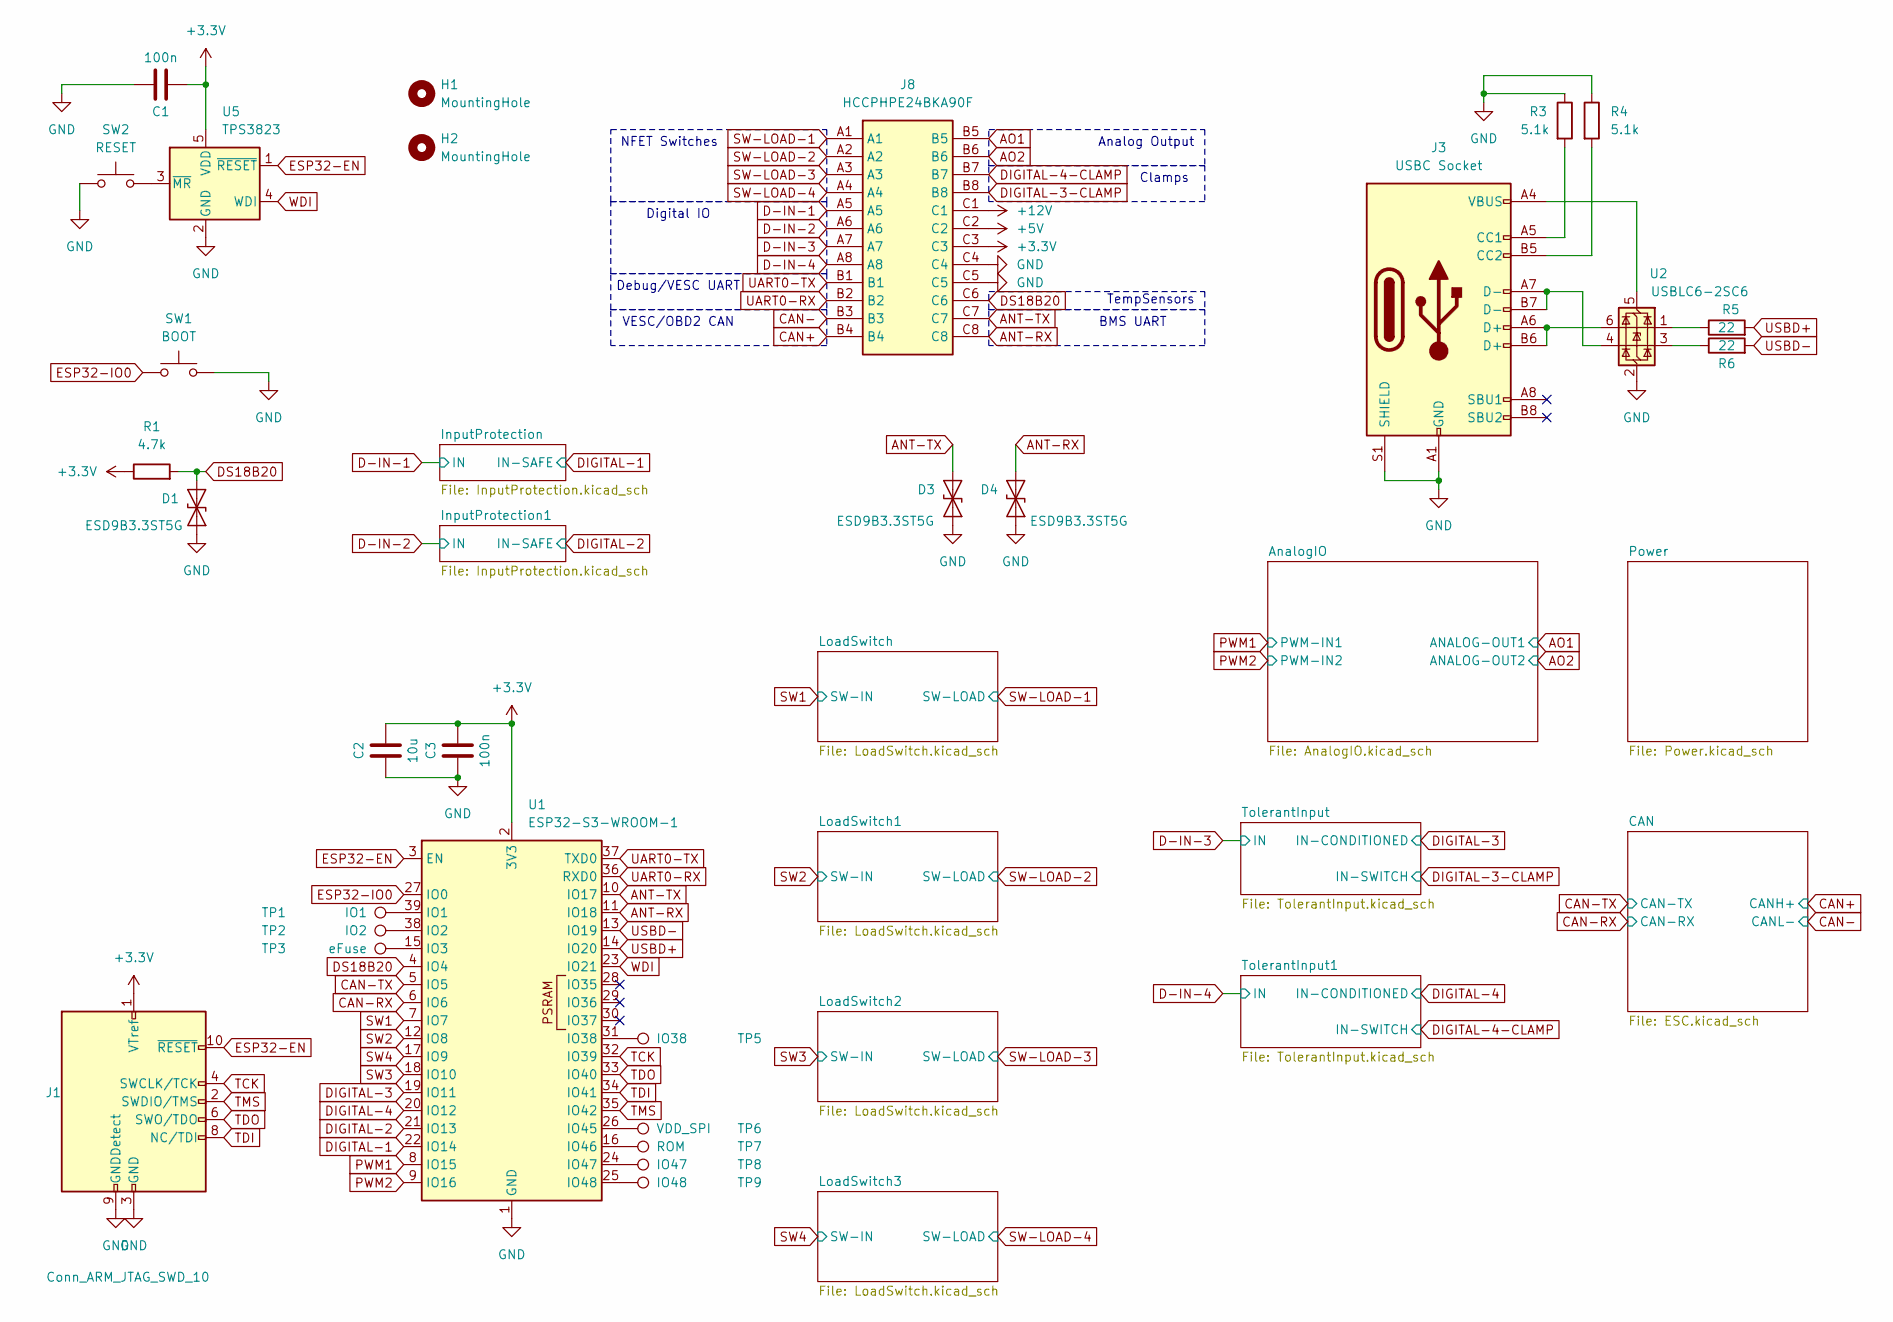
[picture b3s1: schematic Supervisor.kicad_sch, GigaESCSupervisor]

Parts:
C1, C3: 100n; C_0603_1608Metric; MPN C14663
C2: 10u; C_0603_1608Metric; MPN C19702
D1, D3, D4: ESD9B3.3ST5G; D_SOD-923; MPN C96512
H1, H2: MountingHole; MountingHole_3.2mm_M3
J1: Conn_ARM_JTAG_SWD_10; IDC-Header_2x05_P2.54mm_Vertical; MPN C429962
J3: USBC Socket; USB_C_Receptacle_GCT_USB4105-xx-A_16P_TopMnt_Horizontal; MPN C2765186; JLCPosOffset 0,1.27
J8: HCCPHPE24BKA90F; Manufacturer_Part_Number HCCPHPE24BKA90F; Mouser Part Number 649-HCCPHPE24BKA90F
R1: 4.7k; R_0603_1608Metric; MPN C23162
R3, R4: 5.1k; R_0603_1608Metric; MPN C23186
R5, R6: 22; R_0603_1608Metric; MPN C23345
SW1: BOOT; SW_Push_1P1T_XKB_TS-1187A; MPN C318884
SW2: RESET; SW_Push_1P1T_XKB_TS-1187A; MPN C318884
TP1: IO1; TestPoint_Pad_2.0x2.0mm
TP2: IO2; TestPoint_Pad_2.0x2.0mm
TP3: eFuse; TestPoint_Pad_2.0x2.0mm
TP5: IO38; TestPoint_Pad_2.0x2.0mm
TP6: VDD_SPI; TestPoint_Pad_2.0x2.0mm
TP7: ROM; TestPoint_Pad_2.0x2.0mm
TP8: IO47; TestPoint_Pad_2.0x2.0mm
TP9: IO48; TestPoint_Pad_2.0x2.0mm
U1: ESP32-S3-WROOM-1; MPN C2913202
U2: USBLC6-2SC6; SOT-23-6; MPN C2827654; JLCRotOffset -90
U5: TPS3823; SOT-23-5; MPN C7719

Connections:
+3.3V: C1.2, C2.1, C3.1, J1.1 (VTref), J8.C3, R1.1, U1.2 (3V3), U5.5 (VDD); also elsewhere on the board
+5V: J8.C2; also elsewhere on the board
+12V: J8.C1; also elsewhere on the board
ANT-RX: D4.1 (A1), J8.C8, U1.11 (IO18)
ANT-TX: D3.1 (A1), J8.C7, U1.10 (IO17)
AO1: J8.B5; also elsewhere on the board
AO2: J8.B6; also elsewhere on the board
CAN+: J8.B4; also elsewhere on the board
CAN-: J8.B3; also elsewhere on the board
CAN-RX: U1.6 (IO6); also elsewhere on the board
CAN-TX: U1.5 (IO5); also elsewhere on the board
D-IN-3: J8.A7; also elsewhere on the board
D-IN-4: J8.A8; also elsewhere on the board
DIGITAL-1: U1.22 (IO14); also elsewhere on the board
DIGITAL-2: U1.21 (IO13); also elsewhere on the board
DIGITAL-3-CLAMP: J8.B8; also elsewhere on the board
DIGITAL-4-CLAMP: J8.B7; also elsewhere on the board
DS18B20: D1.1 (A1), J8.C6, R1.2, U1.4 (IO4)
ESP32-EN: J1.10 (~RESET), U1.3 (EN), U5.1 (~RESET)
ESP32-IO0: SW1.1, U1.27 (IO0)
GND: C1.1, C2.2, C3.2, D1.2 (A2), D3.2 (A2), D4.2 (A2), J1.3 (GND), J1.5 (GND), J1.9 (GNDDetect), J3.A1 (GND), J3.A12 (GND), J3.B1 (GND), J3.B12 (GND), J3.S1 (SHIELD), J8.C4, J8.C5, R3.1, R4.1, SW1.2, SW2.1, U1.1 (GND), U1.40 (GND), U1.41 (GND), U2.2 (GND), U5.2 (GND); also elsewhere on the board
unnamed: J3.A5 (CC1), R3.2
unnamed: J3.B5 (CC2), R4.2
unnamed: J3.A6 (D+), J3.B6 (D+), U2.6 (I/O1)
unnamed: J3.A7 (D-), J3.B7 (D-), U2.4 (I/O2)
unnamed: R5.1, U2.1 (I/O1)
unnamed: R6.1, U2.3 (I/O2)
unnamed: TP1.1, U1.39 (IO1)
unnamed: TP2.1, U1.38 (IO2)
unnamed: TP3.1, U1.15 (IO3)
unnamed: TP5.1, U1.31 (IO38)
unnamed: TP6.1, U1.26 (IO45)
unnamed: TP7.1, U1.16 (IO46)
unnamed: TP8.1, U1.24 (IO47)
unnamed: TP9.1, U1.25 (IO48)
unnamed: J3.A4 (VBUS), J3.A9 (VBUS), J3.B4 (VBUS), J3.B9 (VBUS), U2.5 (VBUS)
unnamed: SW2.2, U5.3 (~MR)
PWM1: U1.8 (IO15); also elsewhere on the board
PWM2: U1.9 (IO16); also elsewhere on the board
SW1: U1.7 (IO7); also elsewhere on the board
SW2: U1.12 (IO8); also elsewhere on the board
SW3: U1.18 (IO10); also elsewhere on the board
SW4: U1.17 (IO9); also elsewhere on the board
SW-LOAD-1: J8.A1; also elsewhere on the board
SW-LOAD-2: J8.A2; also elsewhere on the board
SW-LOAD-3: J8.A3; also elsewhere on the board
SW-LOAD-4: J8.A4; also elsewhere on the board
TCK: J1.4 (SWCLK/TCK), U1.32 (IO39)
TDI: J1.8 (NC/TDI), U1.34 (IO41)
TDO: J1.6 (SWO/TDO), U1.33 (IO40)
TMS: J1.2 (SWDIO/TMS), U1.35 (IO42)
UART0-RX: J8.B2, U1.36 (RXD0)
UART0-TX: J8.B1, U1.37 (TXD0)
USBD+: R5.2, U1.14 (IO20)
USBD-: R6.2, U1.13 (IO19)
WDI: U1.23 (IO21), U5.4 (WDI)

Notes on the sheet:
TempSensors
Clamps
Digital IO
Analog Output
VESC/OBD2 CAN
NFET Switches
Debug/VESC UART
BMS UART

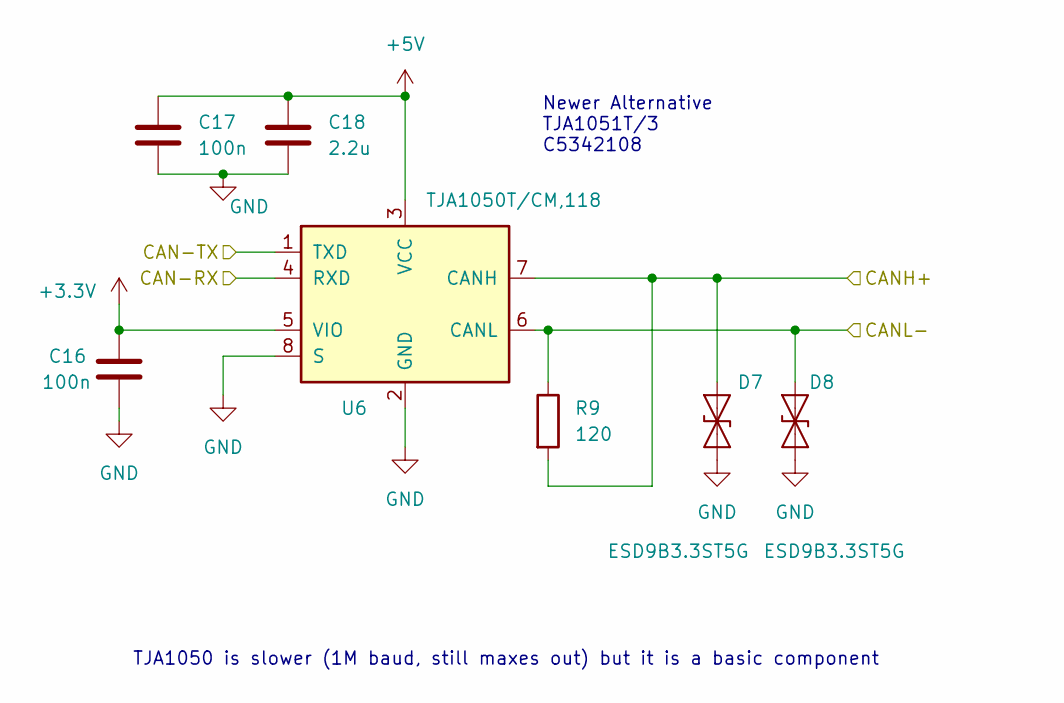
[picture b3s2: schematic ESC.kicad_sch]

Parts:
C16, C17: 100n; C_0603_1608Metric; MPN C14663
C18: 2.2u; C_0603_1608Metric; MPN C23630
D7, D8: ESD9B3.3ST5G; D_SOD-923; MPN C96512
R9: 120; R_0603_1608Metric; MPN C22787
U6: TJA1050T/CM,118; SOIC-8_3.9x4.9mm_P1.27mm; MPN C6952; JLCRotOffset -90

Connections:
+3.3V: C16.1, U6.5 (VIO); also elsewhere on the board
+5V: C17.1, C18.1, U6.3 (VCC); also elsewhere on the board
CAN+: D7.1 (A1), R9.2, U6.7 (CANH); also elsewhere on the board
CAN-: D8.1 (A1), R9.1, U6.6 (CANL); also elsewhere on the board
CAN-RX: U6.4 (RXD); also elsewhere on the board
CAN-TX: U6.1 (TXD); also elsewhere on the board
GND: C16.2, C17.2, C18.2, D7.2 (A2), D8.2 (A2), U6.2 (GND), U6.8 (S); also elsewhere on the board

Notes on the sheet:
TJA1050 is slower (1M baud, still maxes out) but it is a basic component
Newer Alternative TJA1051T/3 C5342108

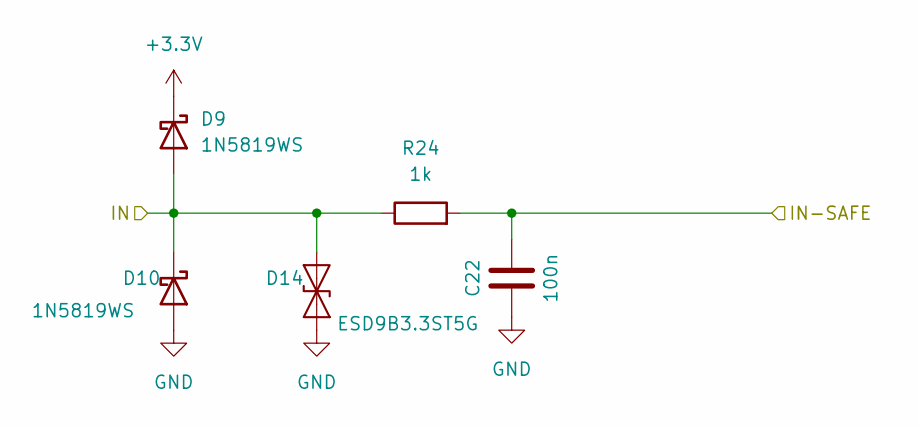
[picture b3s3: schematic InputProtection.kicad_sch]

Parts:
C22: 100n; C_0603_1608Metric; MPN C14663
D9, D10: 1N5819WS; D_SOD-323; MPN C191023
D14: ESD9B3.3ST5G; D_SOD-923; MPN C96512
R24: 1k; R_0603_1608Metric; MPN C21190

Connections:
+3.3V: D9.1 (K); also elsewhere on the board
DIGITAL-1: C22.1, R24.2; also elsewhere on the board
GND: C22.2, D10.2 (A), D14.2 (A2); also elsewhere on the board

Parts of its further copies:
C23: 100n; C_0603_1608Metric; MPN C14663
D11: ESD9B3.3ST5G; D_SOD-923; MPN C96512
D12, D13: 1N5819WS; D_SOD-323; MPN C191023
R25: 1k; R_0603_1608Metric; MPN C21190

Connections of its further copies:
+3.3V: D12.1 (K); also elsewhere on the board
DIGITAL-2: C23.1, R25.2; also elsewhere on the board
GND: C23.2, D11.2 (A2), D13.2 (A); also elsewhere on the board
